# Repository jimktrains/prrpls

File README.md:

# prrpls
PRR Position Light Signal for N-Scale

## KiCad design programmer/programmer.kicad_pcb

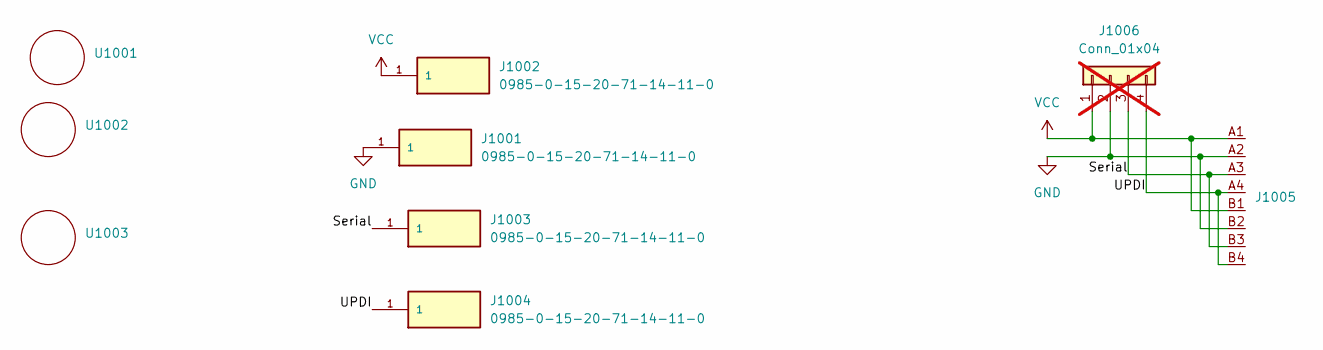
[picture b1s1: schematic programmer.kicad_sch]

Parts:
J1001, J1002, J1003, J1004: 0985-0-15-20-71-14-11-0; MILL-MAX_0985-0-15-20-71-14-11-0; PARTREV 3/8/22; DigiKey_Part_Number ED1122-ND
J1005: 8-pin-clip
J1006: Conn_01x04; PinHeader_1x04_P2.54mm_Vertical; not fitted
U1001, U1002, U1003: 6218-0-00-15-00-00-03-0

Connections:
/Serial: J1003.1, J1005.A3, J1005.B3, J1006.3
/UPDI: J1004.1, J1005.A4, J1005.B4, J1006.4
GND: J1001.1, J1005.A2, J1005.B2, J1006.2
VCC: J1002.1, J1005.A1, J1005.B1, J1006.1

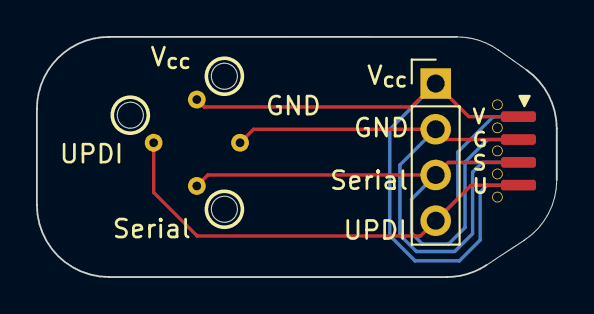
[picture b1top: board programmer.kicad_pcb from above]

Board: 2 copper layers, 28.9 x 13.3 mm, 9 parts (0 on the bottom side), 4 nets.

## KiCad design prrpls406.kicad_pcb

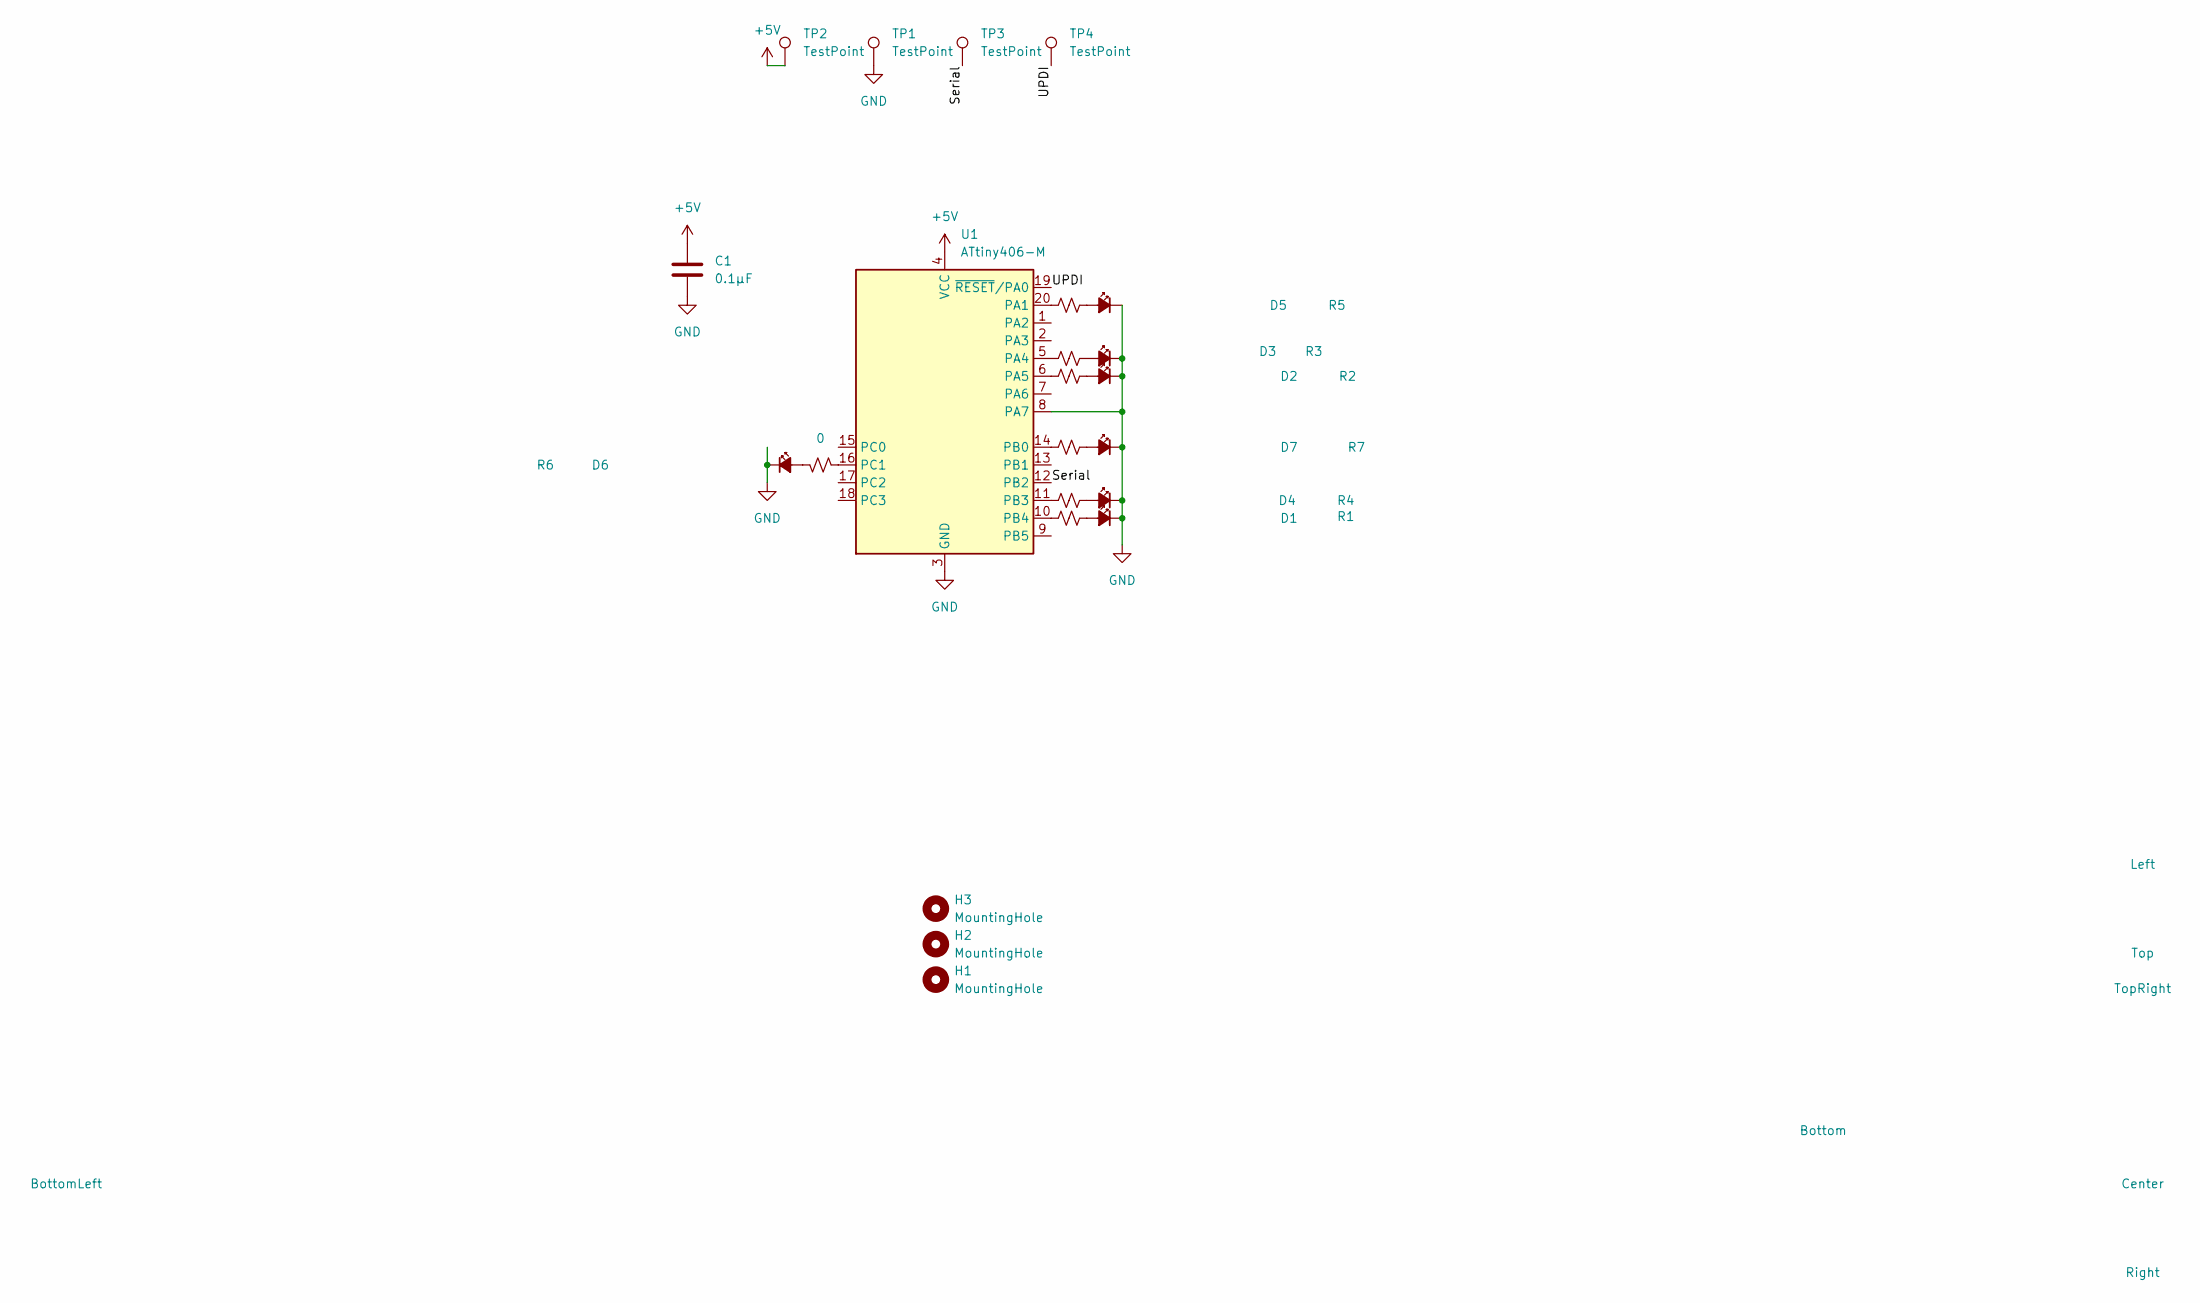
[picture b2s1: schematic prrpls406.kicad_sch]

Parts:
C1: 0.1μF; R_0402_1005Metric_short_lines
D1, D2, D3, D4, D5, D6, D7: LED_Small_Filled; LED_0402_1005Metric
H1, H2, H3: MountingHole; 0.5 npth
R1, R2, R3, R4, R5, R6, R7: 0; Jumpered_R_0402_1005Metric
TP1, TP2, TP3, TP4: TestPoint; 0.5mm-pogo-pad
U1: ATtiny406-M; extra_clearence_VQFN-20-1EP_3x3mm_P0.4mm_EP1.7x1.7mm

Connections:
+5V: C1.1, TP2.1, U1.4 (VCC)
/Serial: TP3.1, U1.12 (PB2)
/UPDI: TP4.1, U1.19 (~RESET/PA0)
GND: C1.2, D1.1 (K), D2.1 (K), D3.1 (K), D4.1 (K), D5.1 (K), D6.1 (K), D7.1 (K), TP1.1, U1.3 (GND), U1.8 (PA7), U1.21 (GND)
unnamed: D1.2 (A), R1.2
unnamed: D2.2 (A), R2.2
unnamed: D3.2 (A), R3.2
unnamed: D4.2 (A), R4.2
unnamed: D5.2 (A), R5.2
unnamed: D6.2 (A), R6.2
unnamed: D7.2 (A), R7.2
unnamed: R5.1, U1.20 (PA1)
unnamed: R3.1, U1.5 (PA4)
unnamed: R2.1, U1.6 (PA5)
unnamed: R7.1, U1.14 (PB0)
unnamed: R4.1, U1.11 (PB3)
unnamed: R1.1, U1.10 (PB4)
unnamed: R6.1, U1.16 (PC1)

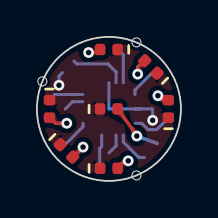
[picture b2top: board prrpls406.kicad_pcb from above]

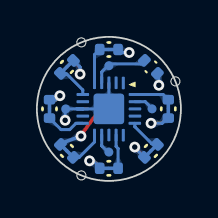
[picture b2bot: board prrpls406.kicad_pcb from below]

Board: 2 copper layers, 8.0 x 8.0 mm, 23 parts (13 on the bottom side), 18 nets.

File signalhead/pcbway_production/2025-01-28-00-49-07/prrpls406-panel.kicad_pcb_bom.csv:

Designator,Quantity,Value,Footprint,Package,MPN,DNP,Mount_Type,Description,Position
"C1, C1, C1, C1, C1, C1, C1, C1, C1",9,0.1μF,R_0402_1005Metric_short_lines,,,,smt,Unpolarized capacitor,
"D1, D1, D1, D1, D1, D1, D1, D1, D1, D2, D2, D2, D2, D2, D2, D2, D2, D2, D3, D3, D3, D3, D3, D3, D3, D3, D3, D4, D4, D4, D4, D4, D4, D4, D4, D4, D5, D5, D5, D5, D5, D5, D5, D5, D5, D6, D6, D6, D6, D6, D6, D6, D6, D6, D7, D7, D7, D7, D7, D7, D7, D7, D7",63,LED_Small_Filled,LED_0402_1005Metric,,,,smt,"Light emitting diode, small symbol, filled shape","[D1,D1,D1,D1,D1,D1,D1,D1,D1]Right; [D2,D2,D2,D2,D2,D2,D2,D2,D2]TopRight; [D3,D3,D3,D3,D3,D3,D3,D3,D3]Top; [D4,D4,D4,D4,D4,D4,D4,D4,D4]Center; [D5,D5,D5,D5,D5,D5,D5,D5,D5]Left; [D6,D6,D6,D6,D6,D6,D6,D6,D6]BottomLeft; [D7,D7,D7,D7,D7,D7,D7,D7,D7]Bottom"
"KiKit_MB_10_2, KiKit_MB_10_3, KiKit_MB_10_4, KiKit_MB_10_5, KiKit_MB_11_2, KiKit_MB_11_3, KiKit_MB_11_4, KiKit_MB_11_5, KiKit_MB_12_2, KiKit_MB_12_3, KiKit_MB_12_4, KiKit_MB_12_5, KiKit_MB_13_2, KiKit_MB_13_3, KiKit_MB_13_4, KiKit_MB_13_5, KiKit_MB_14_2, KiKit_MB_14_3, KiKit_MB_14_4, KiKit_MB_14_5, KiKit_MB_15_2, KiKit_MB_15_3, KiKit_MB_15_4, KiKit_MB_15_5, KiKit_MB_16_2, KiKit_MB_16_3, KiKit_MB_16_4, KiKit_MB_16_5, KiKit_MB_17_2, KiKit_MB_17_3, KiKit_MB_17_4, KiKit_MB_17_5, KiKit_MB_18_2, KiKit_MB_18_3, KiKit_MB_18_4, KiKit_MB_18_5, KiKit_MB_19_2, KiKit_MB_19_3, KiKit_MB_19_4, KiKit_MB_19_5, KiKit_MB_1_2, KiKit_MB_1_3, KiKit_MB_1_4, KiKit_MB_1_5, KiKit_MB_20_2, KiKit_MB_20_3, KiKit_MB_20_4, KiKit_MB_20_5, KiKit_MB_21_2, KiKit_MB_21_3, KiKit_MB_21_4, KiKit_MB_21_5, KiKit_MB_22_2, KiKit_MB_22_3, KiKit_MB_22_4, KiKit_MB_22_5, KiKit_MB_23_2, KiKit_MB_23_3, KiKit_MB_23_4, KiKit_MB_23_5, KiKit_MB_24_2, KiKit_MB_24_3, KiKit_MB_24_4, KiKit_MB_24_5, KiKit_MB_25_2, KiKit_MB_25_3, KiKit_MB_25_4, KiKit_MB_25_5, KiKit_MB_26_2, KiKit_MB_26_3, KiKit_MB_26_4, KiKit_MB_26_5, KiKit_MB_27_2, KiKit_MB_27_3, KiKit_MB_27_4, KiKit_MB_27_5, KiKit_MB_2_2, KiKit_MB_2_3, KiKit_MB_2_4, KiKit_MB_2_5, KiKit_MB_3_2, KiKit_MB_3_3, KiKit_MB_3_4, KiKit_MB_3_5, KiKit_MB_4_2, KiKit_MB_4_3, KiKit_MB_4_4, KiKit_MB_4_5, KiKit_MB_5_2, KiKit_MB_5_3, KiKit_MB_5_4, KiKit_MB_5_5, KiKit_MB_6_2, KiKit_MB_6_3, KiKit_MB_6_4, KiKit_MB_6_5, KiKit_MB_7_2, KiKit_MB_7_3, KiKit_MB_7_4, KiKit_MB_7_5, KiKit_MB_8_2, KiKit_MB_8_3, KiKit_MB_8_4, KiKit_MB_8_5, KiKit_MB_9_2, KiKit_MB_9_3, KiKit_MB_9_4, KiKit_MB_9_5",108,NPTH,NPTH,,,,tht,,
"R1, R1, R1, R1, R1, R1, R1, R1, R1, R2, R2, R2, R2, R2, R2, R2, R2, R2, R3, R3, R3, R3, R3, R3, R3, R3, R3, R4, R4, R4, R4, R4, R4, R4, R4, R4, R5, R5, R5, R5, R5, R5, R5, R5, R5, R6, R6, R6, R6, R6, R6, R6, R6, R6, R7, R7, R7, R7, R7, R7, R7, R7, R7",63,0,Jumpered_R_0402_1005Metric,,,,smt,"Resistor, small US symbol",
"TP1, TP1, TP1, TP1, TP1, TP1, TP1, TP1, TP1, TP2, TP2, TP2, TP2, TP2, TP2, TP2, TP2, TP2, TP3, TP3, TP3, TP3, TP3, TP3, TP3, TP3, TP3, TP4, TP4, TP4, TP4, TP4, TP4, TP4, TP4, TP4",36,TestPoint,0.5mm-pogo-pad,,,,tht,test point,
"U1, U1, U1, U1, U1, U1, U1, U1, U1",9,ATtiny406-M,extra_clearence_VQFN-20-1EP_3x3mm_P0.4mm_EP1.7x1.7mm,,,,smt,"20MHz, 4kB Flash, 256B SRAM, 128B EEPROM, VQFN-20",

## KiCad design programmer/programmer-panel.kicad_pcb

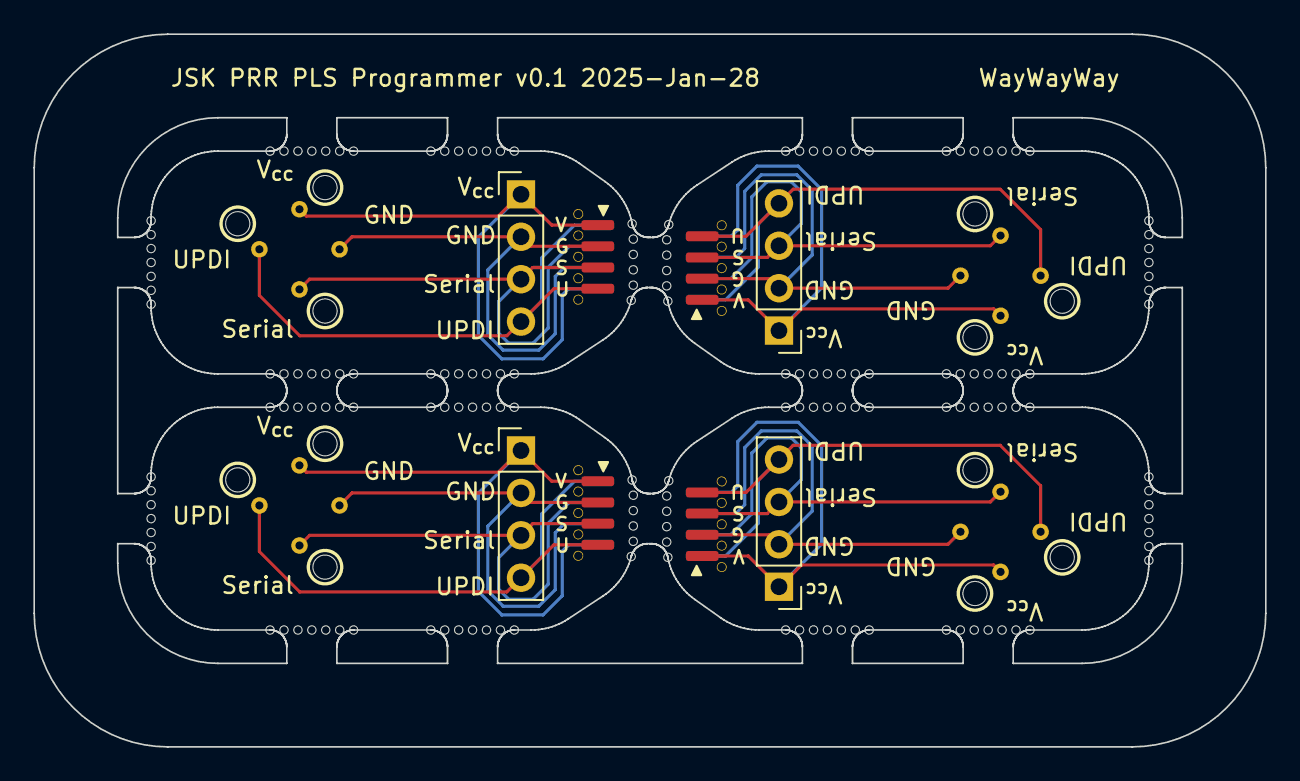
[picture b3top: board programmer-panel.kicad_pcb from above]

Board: 2 copper layers, 73.8 x 42.7 mm, 200 parts (0 on the bottom side), 16 nets.

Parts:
J1001, J1001#2, J1001#3, J1001#4, J1002, J1002#2, J1002#3, J1002#4, J1003, J1003#2, J1003#3, J1003#4, J1004, J1004#2, J1004#3, J1004#4: 0985-0-15-20-71-14-11-0; MILL-MAX_0985-0-15-20-71-14-11-0
J1005, J1005#2, J1005#3, J1005#4: 8-pin-clip
J1006, J1006#2, J1006#3, J1006#4: Conn_01x04; PinHeader_1x04_P2.54mm_Vertical
KiKit_MB_1_1, KiKit_MB_1_2, KiKit_MB_1_3, KiKit_MB_1_4, KiKit_MB_1_5, KiKit_MB_1_6, KiKit_MB_1_7, KiKit_MB_2_1, KiKit_MB_2_2, KiKit_MB_2_3, KiKit_MB_2_4, KiKit_MB_2_5, KiKit_MB_2_6, KiKit_MB_3_1, KiKit_MB_3_2, KiKit_MB_3_3, KiKit_MB_3_4, KiKit_MB_3_5, KiKit_MB_3_6, KiKit_MB_3_7, KiKit_MB_4_1, KiKit_MB_4_2, KiKit_MB_4_3, KiKit_MB_4_4, KiKit_MB_4_5, KiKit_MB_4_6, KiKit_MB_4_7, KiKit_MB_5_1, KiKit_MB_5_2, KiKit_MB_5_3, KiKit_MB_5_4, KiKit_MB_5_5, KiKit_MB_5_6, KiKit_MB_5_7, KiKit_MB_6_1, KiKit_MB_6_2, KiKit_MB_6_3, KiKit_MB_6_4, KiKit_MB_6_5, KiKit_MB_6_6, KiKit_MB_6_7, KiKit_MB_7_1, KiKit_MB_7_2, KiKit_MB_7_3, KiKit_MB_7_4, KiKit_MB_7_5, KiKit_MB_7_6, KiKit_MB_8_1, KiKit_MB_8_2, KiKit_MB_8_3, KiKit_MB_8_4, KiKit_MB_8_5, KiKit_MB_8_6, KiKit_MB_8_7, KiKit_MB_9_1, KiKit_MB_9_2, KiKit_MB_9_3, KiKit_MB_9_4, KiKit_MB_9_5, KiKit_MB_9_6, KiKit_MB_9_7, KiKit_MB_10_1, KiKit_MB_10_2, KiKit_MB_10_3, KiKit_MB_10_4, KiKit_MB_10_5, KiKit_MB_10_6, KiKit_MB_10_7, KiKit_MB_11_1, KiKit_MB_11_2, KiKit_MB_11_3, KiKit_MB_11_4, KiKit_MB_11_5, KiKit_MB_11_6, KiKit_MB_11_7, KiKit_MB_12_1, KiKit_MB_12_2, KiKit_MB_12_3, KiKit_MB_12_4, KiKit_MB_12_5, KiKit_MB_12_6, KiKit_MB_12_7, KiKit_MB_13_1, KiKit_MB_13_2, KiKit_MB_13_3, KiKit_MB_13_4, KiKit_MB_13_5, KiKit_MB_13_6, KiKit_MB_13_7, KiKit_MB_14_1, KiKit_MB_14_2, KiKit_MB_14_3, KiKit_MB_14_4, KiKit_MB_14_5, KiKit_MB_14_6, KiKit_MB_15_1, KiKit_MB_15_2, KiKit_MB_15_3, KiKit_MB_15_4, KiKit_MB_15_5, KiKit_MB_15_6, KiKit_MB_15_7, KiKit_MB_16_1, KiKit_MB_16_2, KiKit_MB_16_3, KiKit_MB_16_4, KiKit_MB_16_5, KiKit_MB_16_6, KiKit_MB_16_7, KiKit_MB_17_1, KiKit_MB_17_2, KiKit_MB_17_3, KiKit_MB_17_4, KiKit_MB_17_5, KiKit_MB_17_6, KiKit_MB_17_7, KiKit_MB_18_1, KiKit_MB_18_2, KiKit_MB_18_3, KiKit_MB_18_4, KiKit_MB_18_5, KiKit_MB_18_6, KiKit_MB_18_7, KiKit_MB_19_1, KiKit_MB_19_2, KiKit_MB_19_3, KiKit_MB_19_4, KiKit_MB_19_5, KiKit_MB_19_6, KiKit_MB_20_1, KiKit_MB_20_2, KiKit_MB_20_3, KiKit_MB_20_4, KiKit_MB_20_5, KiKit_MB_20_6, KiKit_MB_20_7, KiKit_MB_21_1, KiKit_MB_21_2, KiKit_MB_21_3, KiKit_MB_21_4, KiKit_MB_21_5, KiKit_MB_21_6, KiKit_MB_21_7, KiKit_MB_22_1, KiKit_MB_22_2, KiKit_MB_22_3, KiKit_MB_22_4, KiKit_MB_22_5, KiKit_MB_22_6, KiKit_MB_22_7, KiKit_MB_23_1, KiKit_MB_23_2, KiKit_MB_23_3, KiKit_MB_23_4, KiKit_MB_23_5, KiKit_MB_23_6, KiKit_MB_23_7, KiKit_MB_24_1, KiKit_MB_24_2, KiKit_MB_24_3, KiKit_MB_24_4, KiKit_MB_24_5, KiKit_MB_24_6, KiKit_MB_24_7: NPTH
U1001, U1001#2, U1001#3, U1001#4, U1002, U1002#2, U1002#3, U1002#4, U1003, U1003#2, U1003#3, U1003#4: 6218-0-00-15-00-00-03-0

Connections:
Board_0-/Serial: J1003#3.1, J1005#3.A3, J1005#3.B3, J1006.3
Board_0-/UPDI: J1004#2.1, J1005#3.A4, J1005#3.B4, J1006.4
Board_0-GND: J1001#2.1, J1005#3.A2, J1005#3.B2, J1006.2
Board_0-VCC: J1002#3.1, J1005#3.A1, J1005#3.B1, J1006.1
Board_1-/Serial: J1003#4.1, J1005.A3, J1005.B3, J1006#3.3
Board_1-/UPDI: J1004#3.1, J1005.A4, J1005.B4, J1006#3.4
Board_1-GND: J1001.1, J1005.A2, J1005.B2, J1006#3.2
Board_1-VCC: J1002.1, J1005.A1, J1005.B1, J1006#3.1
Board_2-/Serial: J1003#2.1, J1005#4.A3, J1005#4.B3, J1006#4.3
Board_2-/UPDI: J1004#4.1, J1005#4.A4, J1005#4.B4, J1006#4.4
Board_2-GND: J1001#4.1, J1005#4.A2, J1005#4.B2, J1006#4.2
Board_2-VCC: J1002#2.1, J1005#4.A1, J1005#4.B1, J1006#4.1
Board_3-/Serial: J1003.1, J1005#2.A3, J1005#2.B3, J1006#2.3
Board_3-/UPDI: J1004.1, J1005#2.A4, J1005#2.B4, J1006#2.4
Board_3-GND: J1001#3.1, J1005#2.A2, J1005#2.B2, J1006#2.2
Board_3-VCC: J1002#4.1, J1005#2.A1, J1005#2.B1, J1006#2.1

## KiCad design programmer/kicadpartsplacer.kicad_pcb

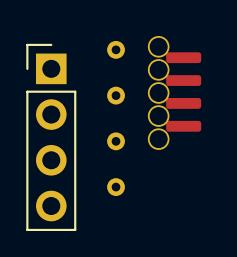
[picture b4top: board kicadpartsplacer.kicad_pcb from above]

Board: 2 copper layers, 9 parts (0 on the bottom side), 4 nets, no tracks yet.

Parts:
J1001, J1002, J1003, J1004: 0985-0-15-20-71-14-11-0; MILL-MAX_0985-0-15-20-71-14-11-0
J1005: 8-pin-clip
J1006: Conn_01x04; PinHeader_1x04_P2.54mm_Vertical
U1001, U1002, U1003: 6218-0-00-15-00-00-03-0

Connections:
/Serial: J1003.1, J1005.3, J1005.6, J1006.3
/UPDI: J1004.1, J1005.4, J1005.5, J1006.4
GND: J1002.1, J1005.2, J1005.7, J1006.2
VCC: J1001.1, J1005.1, J1005.8, J1006.1

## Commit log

2025-01-27 init
2025-01-28 made a new panel
2025-01-28 submitting
2025-01-28 subdirectory
2025-01-28 adding the programmer
2025-01-28 final update
2025-01-28 adding c .gitignore
2025-01-28 .gitignore netbeans
2025-01-28 added submitted gerber files
